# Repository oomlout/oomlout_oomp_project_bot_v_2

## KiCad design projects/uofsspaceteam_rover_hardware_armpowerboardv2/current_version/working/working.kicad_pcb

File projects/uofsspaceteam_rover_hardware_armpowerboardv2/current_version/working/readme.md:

# rover_hardware
 
## summary 
* id: uofsspaceteam_rover_hardware_armpowerboardv2
* user: uofsspaceteam
* name: rover_hardware
* board: armpowerboardv2
* repo: https://github.com/UofSSpaceTeam/rover-hardware
* src_file_repo_kicad_pcb: Projects/Arm/ArmPowerBoardV2/ArmPowerBoardV2.kicad_pcb
* src_file_repo_kicad_pcb_link: https://github.com/UofSSpaceTeam/rover-hardware/tree/master/Projects/Arm/ArmPowerBoardV2/ArmPowerBoardV2.kicad_pcb

* src_file_repo_sch: Projects/Arm/ArmPowerBoardV2/ArmPowerBoardV2.sch
* src_file_repo_sch_link: https://github.com/UofSSpaceTeam/rover-hardware/tree/master/Projects/Arm/ArmPowerBoardV2/ArmPowerBoardV2.sch
* full details link: https://github.com/oomlout/oomlout_oomp_project_bot_v_2/tree/main/projects/uofsspaceteam_rover_hardware_armpowerboardv2/current_version/working

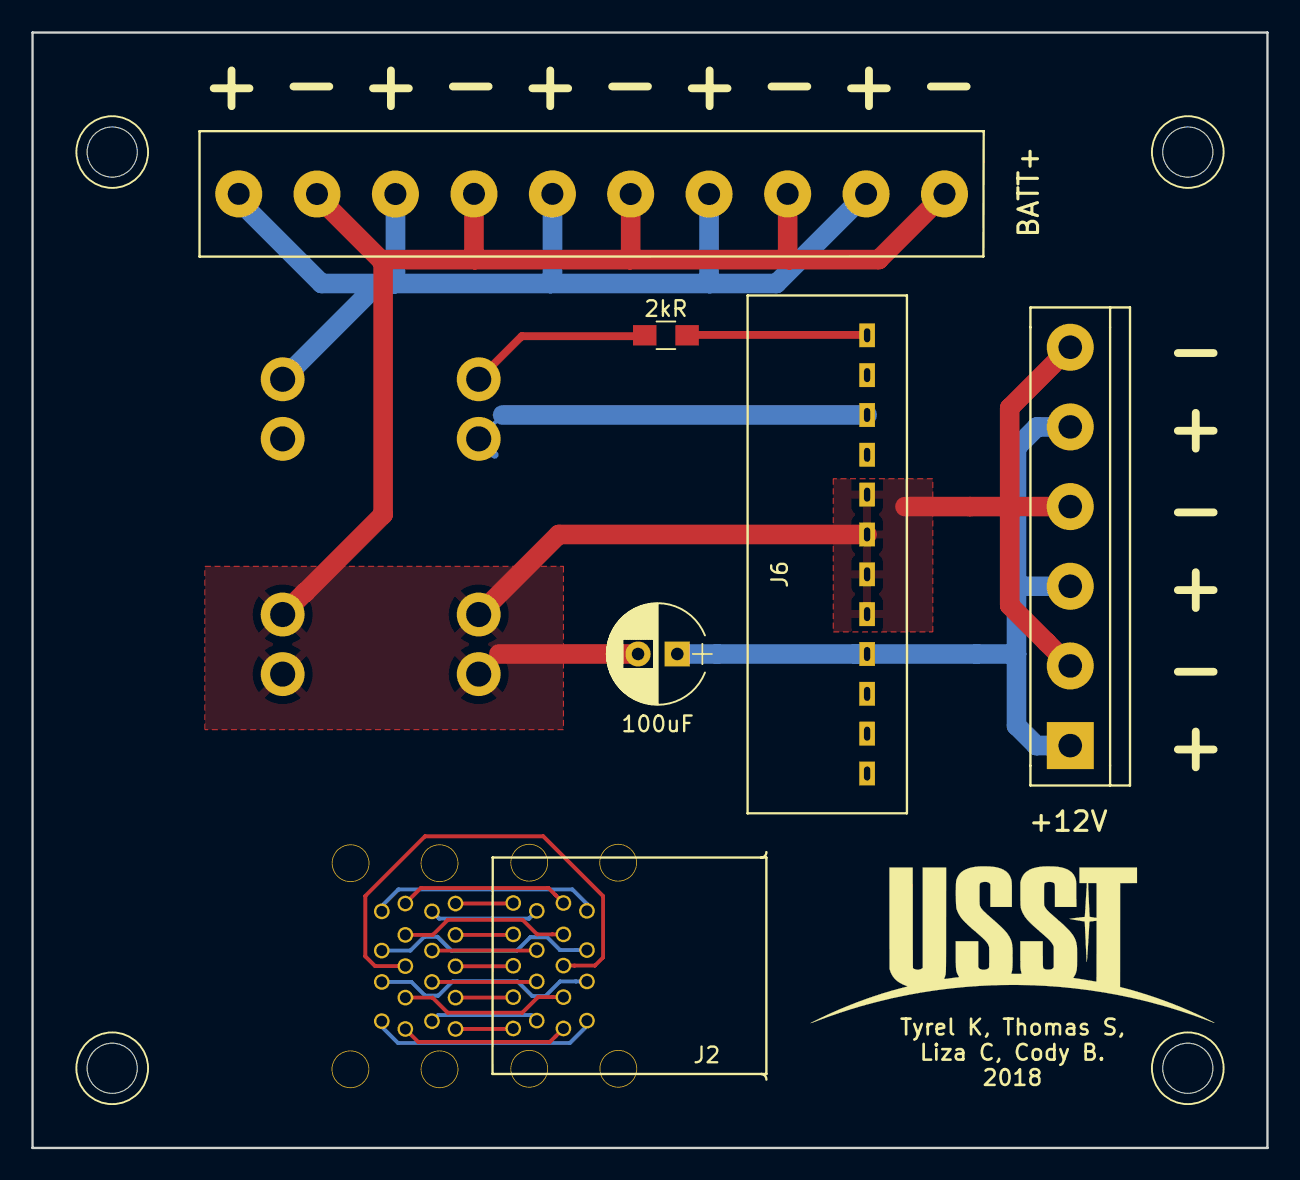
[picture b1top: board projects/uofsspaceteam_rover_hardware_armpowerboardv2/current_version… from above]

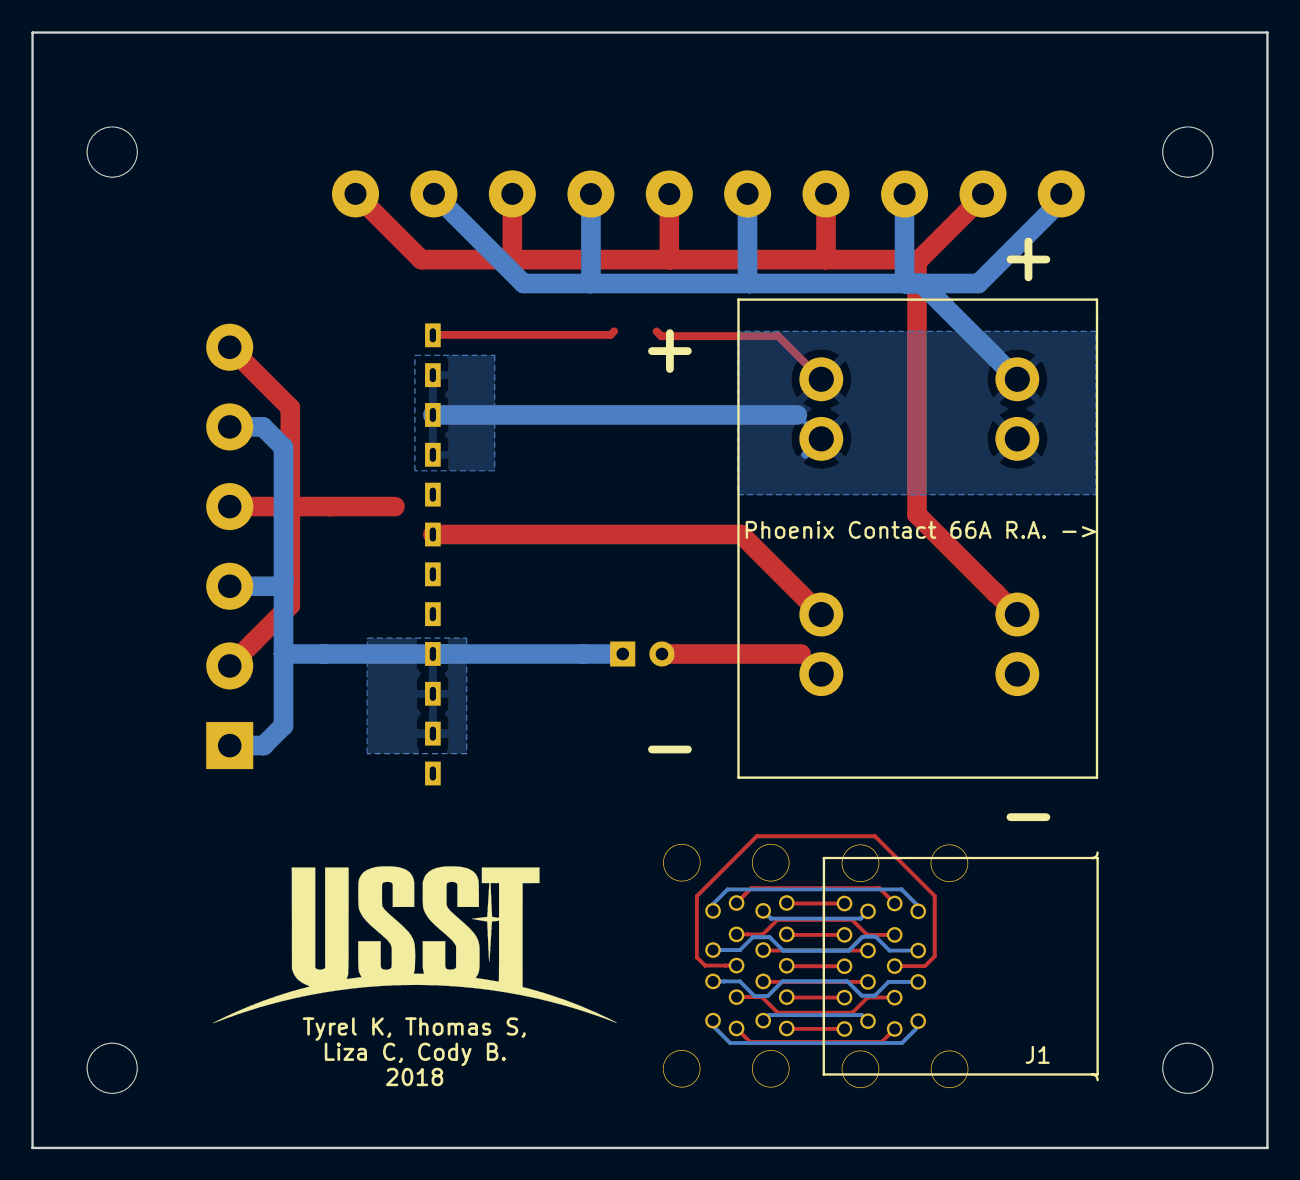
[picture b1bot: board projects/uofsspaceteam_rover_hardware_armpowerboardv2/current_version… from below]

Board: 2 copper layers, 78.7 x 71.1 mm, 8 parts (2 on the bottom side), 22 nets.

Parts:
2kR: 2kR; R_0805_HandSoldering
100uF: 100uF; CP_Radial_D6.3mm_P2.50mm
+12V: 1x6 Conn +12V; TerminalBlock_Pheonix_PT-5mm_6pol
BATT+: 1x10 Conn Batt+; Phoenix_Contact_Terminal_Block_1x10_1935242
J1, J2: USB 3.0 A Stacked; USB-A_3.0_Stacked_WM10420-ND
J6: R-6212P 12V DC Regulator; R-6212P_14-34VDC-12VDC_Converter
Phoenix Contact 66A R.A. ->: Phoenix Contact Batt; Phoenix_Contact_1770539

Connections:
+12V: 100uF.1, +12V.1, +12V.3, +12V.5, J6.9, J6.10, J6.11
BATT+: 2kR.1, BATT+.1, BATT+.3, BATT+.5, BATT+.7, BATT+.9, J6.2, J6.3, J6.4, Phoenix Contact 66A R.A. ->.1
GND: 100uF.2, +12V.2, +12V.4, +12V.6, BATT+.2, BATT+.4, BATT+.6, BATT+.8, BATT+.10, J6.5, J6.6, J6.7, J6.8, Phoenix Contact 66A R.A. ->.2
unnamed: J1.1, J2.1
unnamed: J1.2, J2.2
unnamed: J1.3, J2.3
unnamed: J1.4, J2.4
unnamed: J1.5, J2.5
unnamed: J1.6, J2.6
unnamed: J1.7, J2.7
unnamed: J1.8, J2.8
unnamed: J1.9, J2.9
unnamed: J1.10, J2.10
unnamed: J1.11, J2.11
unnamed: J1.12, J2.12
unnamed: J1.13, J2.13
unnamed: J1.14, J2.14
unnamed: J1.15, J2.15
unnamed: J1.16, J2.16
unnamed: J1.17, J2.17
unnamed: J1.18, J2.18
unnamed: 2kR.2, J6.1

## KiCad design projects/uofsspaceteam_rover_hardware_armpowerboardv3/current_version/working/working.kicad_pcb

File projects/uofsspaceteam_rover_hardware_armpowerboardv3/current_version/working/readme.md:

# rover_hardware
 
## summary 
* id: uofsspaceteam_rover_hardware_armpowerboardv3
* user: uofsspaceteam
* name: rover_hardware
* board: armpowerboardv3
* repo: https://github.com/UofSSpaceTeam/rover-hardware
* src_file_repo_kicad_pcb: Projects/Arm/ArmPowerBoardV3/ArmPowerBoardV3/ArmPowerBoardV3.kicad_pcb
* src_file_repo_kicad_pcb_link: https://github.com/UofSSpaceTeam/rover-hardware/tree/master/Projects/Arm/ArmPowerBoardV3/ArmPowerBoardV3/ArmPowerBoardV3.kicad_pcb

* src_file_repo_brd: Projects/Arm/ArmPowerBoardV3/ArmPowerBoardV3/FT232RL_USB_Breakout-V_3.7/Hardware/FT232R-Breakout.brd
* src_file_repo_brd_link: https://github.com/UofSSpaceTeam/rover-hardware/tree/master/Projects/Arm/ArmPowerBoardV3/ArmPowerBoardV3/FT232RL_USB_Breakout-V_3.7/Hardware/FT232R-Breakout.brd
* src_file_repo_sch: Projects/Arm/ArmPowerBoardV3/ArmPowerBoardV3/ArmPowerBoardV3.sch
* src_file_repo_sch_link: https://github.com/UofSSpaceTeam/rover-hardware/tree/master/Projects/Arm/ArmPowerBoardV3/ArmPowerBoardV3/ArmPowerBoardV3.sch
* full details link: https://github.com/oomlout/oomlout_oomp_project_bot_v_2/tree/main/projects/uofsspaceteam_rover_hardware_armpowerboardv3/current_version/working

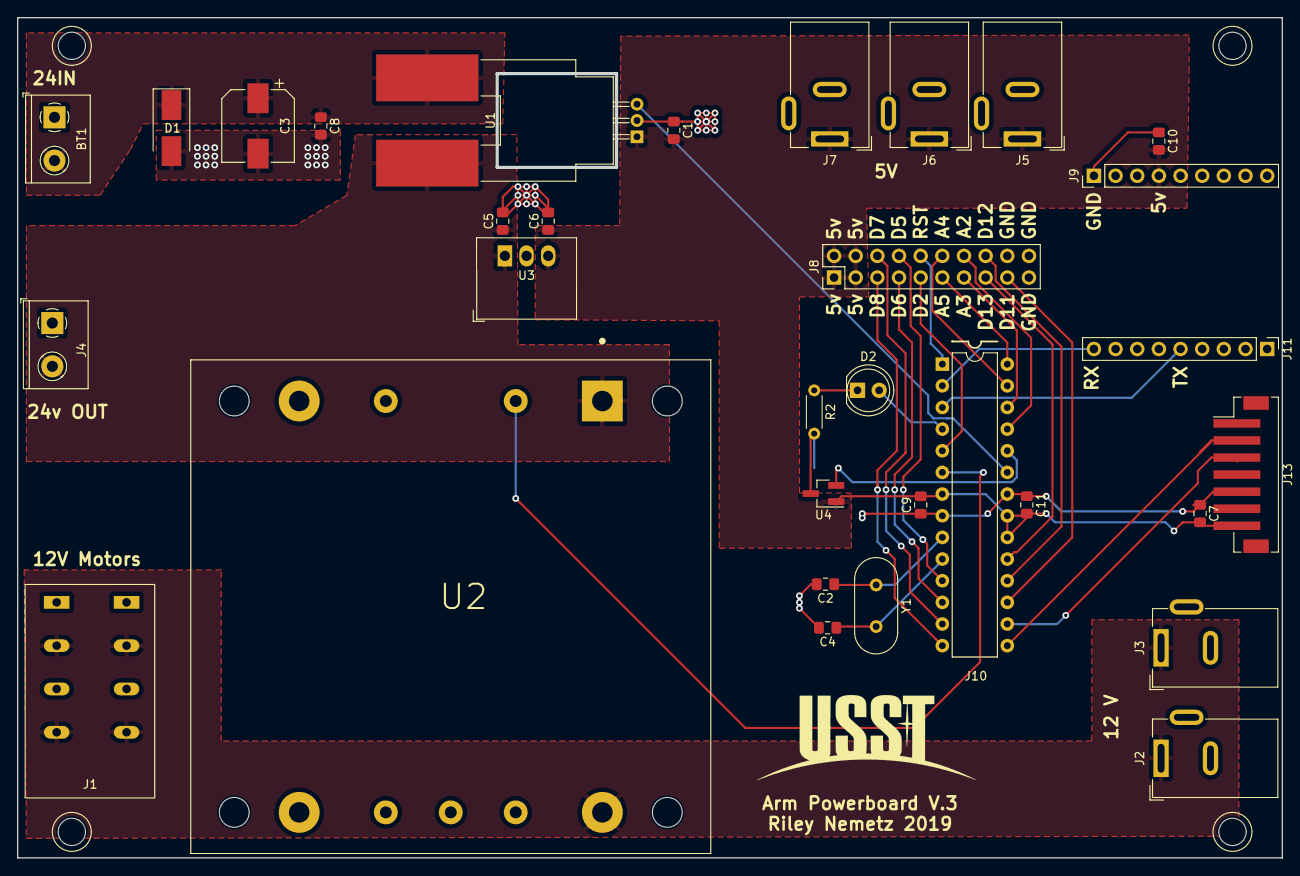
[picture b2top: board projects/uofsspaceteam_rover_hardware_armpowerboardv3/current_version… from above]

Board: 2 copper layers, 148.3 x 98.6 mm, 32 parts (0 on the bottom side), 30 nets.

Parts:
BT1: 24vin; TerminalBlock_1x02_P5.08mm_Horizontal
C1, C7, C9, C10, C11: 100nF; C_0805_2012Metric_Pad1.15x1.40mm_HandSolder
C2, C4: 22pF; C_0805_2012Metric_Pad1.15x1.40mm_HandSolder
C3: 220uF; CP_Elec_8x10
C5, C6: 10pF; C_0805_2012Metric_Pad1.15x1.40mm_HandSolder
C8: 10 uF; C_0805_2012Metric_Pad1.15x1.40mm_HandSolder
D1: D_Zener; D_SMB_Handsoldering
D2: LED; LED_D5.0mm_IRGrey
J1: Screw_Terminal_01x04; TerminalBlock_Big4pin
J2, J3, J5, J6, J7: Barrel_Jack; BarrelJack_Wuerth_6941xx301002
J4: Screw_Terminal_01x02; TerminalBlock_1x02_P5.08mm_Horizontal
J8: Gpio out; PinHeader_2x10_P2.54mm_Vertical
J9: Breakout L; PinHeader_1x09_P2.54mm_Vertical
J10: Atmega Holder; DIP-28_W7.62mm
J11: Breakout R; PinHeader_1x09_P2.54mm_Vertical
J13: JST serial; JST_PH_B7B-PH-SM4-TB_1x07-1MP_P2.00mm_Vertical
R2: R; R_Axial_DIN0204_L3.6mm_D1.6mm_P5.08mm_Horizontal
U1: ACS758; Allegro_CB_PSF
U2: VHB200W-Q24-S12; CONV_VHB200W-Q24-S12
U3: V7805-1000
U4: Temp sense; SOT-23_Handsoldering
Y1: Crystal; Crystal_HC49-U_Vertical

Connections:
5v+: C1.2, C6.1, C7.2, C9.2, C10.2, C11.2, J5.1, J6.1, J7.1, J8.1, J8.2, J8.3, J8.4, J9.4, J10.7, J10.20, J10.21, J13.7, U1.1, U3.3, U4.1
12v+: J1.2, J1.4, J2.1, J3.1, U2.9
12v-: J1.1, J1.3, J2.2, J3.2, U2.5
24v: C5.1, J4.2, U1.5, U2.1, U3.1
GND: BT1.1, C1.1, C2.2, C3.2, C4.2, C5.2, C6.2, C7.1, C8.2, C9.1, C10.1, C11.1, D1.2, J4.1, J5.2, J6.2, J7.2, J8.18, J8.19, J8.20, J9.1, J10.8, J10.22, J13.5, R2.2, U1.2, U2.4, U3.2, U4.3
ISense: J10.23, U1.3
unnamed: BT1.2, C3.1, C8.1, D1.1, U1.4
unnamed: C2.1, J10.9, Y1.1
unnamed: C4.1, J10.10, Y1.2
unnamed: D2.1, R2.1
unnamed: D2.2, J10.4
unnamed: J8.10, J10.1
unnamed: J8.9, J10.5
unnamed: J8.8, J10.11
unnamed: J8.7, J10.12
unnamed: J8.6, J10.13
unnamed: J8.5, J10.14
unnamed: J8.17, J10.17
unnamed: J8.16, J10.18
unnamed: J8.15, J10.19
unnamed: J8.14, J10.25
unnamed: J8.13, J10.26
unnamed: J8.12, J10.27
unnamed: J8.11, J10.28
ONoff: J10.6, U2.2
RX1: J10.15, J13.2
Rx: J10.2, J11.9
TX1: J10.16, J13.3
TempSense: J10.24, U4.2
Tx: J10.3, J11.5

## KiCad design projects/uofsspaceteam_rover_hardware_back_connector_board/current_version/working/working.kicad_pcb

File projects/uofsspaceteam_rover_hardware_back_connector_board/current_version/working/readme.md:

# rover_hardware
 
## summary 
* id: uofsspaceteam_rover_hardware_back_connector_board
* user: uofsspaceteam
* name: rover_hardware
* board: back_connector_board
* repo: https://github.com/UofSSpaceTeam/rover-hardware
* src_file_repo_kicad_pcb: Projects/Power Distribution/Back Connector Board/Back Connector Board.kicad_pcb
* src_file_repo_kicad_pcb_link: https://github.com/UofSSpaceTeam/rover-hardware/tree/master/Projects/Power Distribution/Back Connector Board/Back Connector Board.kicad_pcb
* src_file_repo_kicad_sch: Projects/Power Distribution/ACS712_Testing/ACS712.kicad_sch
* src_file_repo_kicad_sch_link: https://github.com/UofSSpaceTeam/rover-hardware/tree/master/Projects/Power Distribution/ACS712_Testing/ACS712.kicad_sch
* src_file_repo_brd: Projects/Communication/KiCad_USB/modified_eagle_files/RH025.1.brd
* src_file_repo_brd_link: https://github.com/UofSSpaceTeam/rover-hardware/tree/master/Projects/Communication/KiCad_USB/modified_eagle_files/RH025.1.brd
* src_file_repo_sch: Projects/Power Distribution/Back Connector Board/Back Connector Board.sch
* src_file_repo_sch_link: https://github.com/UofSSpaceTeam/rover-hardware/tree/master/Projects/Power Distribution/Back Connector Board/Back Connector Board.sch
* full details link: https://github.com/oomlout/oomlout_oomp_project_bot_v_2/tree/main/projects/uofsspaceteam_rover_hardware_back_connector_board/current_version/working

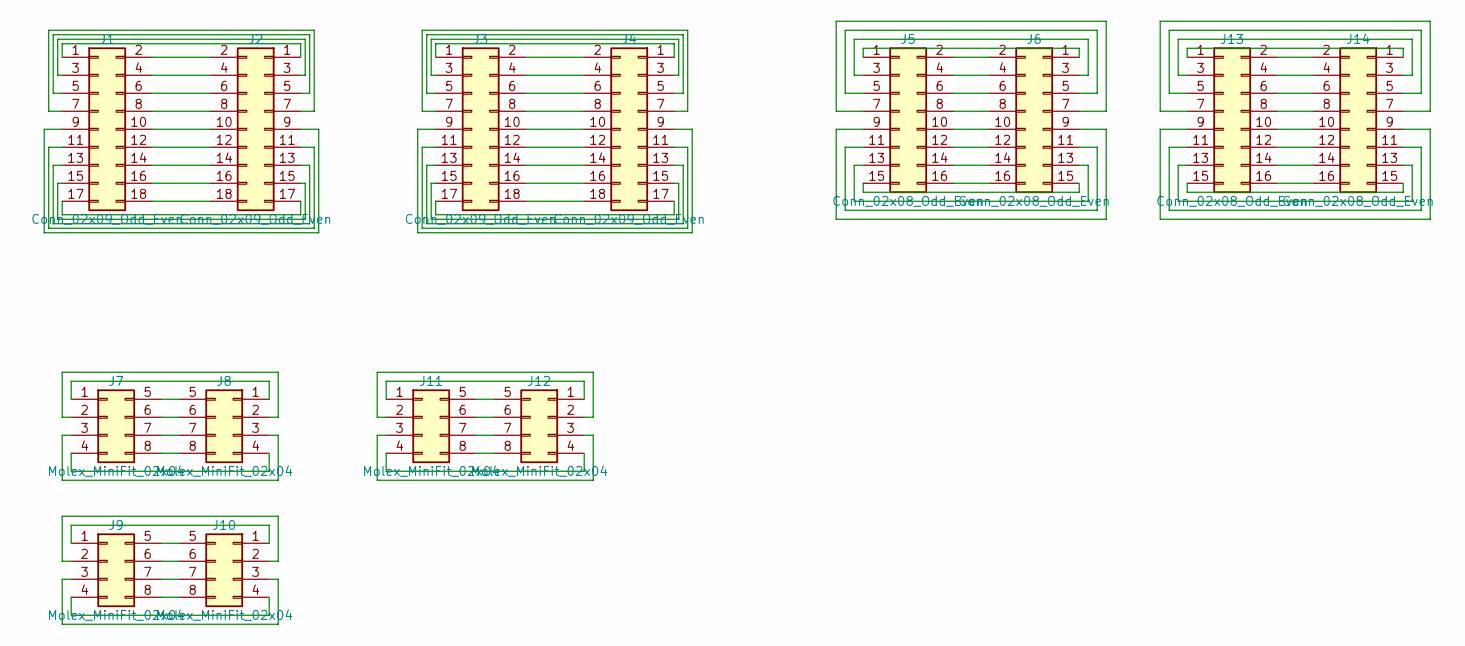
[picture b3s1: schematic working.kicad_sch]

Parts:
J1, J2, J3, J4: Conn_02x09_Odd_Even; USBA_3.0_Stacked_Vertical-Molex_48409
J5, J6, J13, J14: Conn_02x08_Odd_Even; Pin_Header_Straight_2x08_Pitch2.54mm
J7, J8, J9, J10, J11, J12: Molex_MiniFit_02x04; Molex_MiniFit-JR_5566-08A_02x04x4.2_Vertical

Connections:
unnamed: J1.1, J2.1
unnamed: J1.2, J2.2
unnamed: J1.3, J2.3
unnamed: J1.4, J2.4
unnamed: J1.5, J2.5
unnamed: J1.6, J2.6
unnamed: J1.7, J2.7
unnamed: J1.8, J2.8
unnamed: J1.9, J2.9
unnamed: J1.10, J2.10
unnamed: J1.11, J2.11
unnamed: J1.12, J2.12
unnamed: J1.13, J2.13
unnamed: J1.14, J2.14
unnamed: J1.15, J2.15
unnamed: J1.16, J2.16
unnamed: J1.17, J2.17
unnamed: J1.18, J2.18
unnamed: J3.1, J4.1
unnamed: J3.2, J4.2
unnamed: J3.3, J4.3
unnamed: J3.4, J4.4
unnamed: J3.5, J4.5
unnamed: J3.6, J4.6
unnamed: J3.7, J4.7
unnamed: J3.8, J4.8
unnamed: J3.9, J4.9
unnamed: J3.10, J4.10
unnamed: J3.11, J4.11
unnamed: J3.12, J4.12
unnamed: J3.13, J4.13
unnamed: J3.14, J4.14
unnamed: J3.15, J4.15
unnamed: J3.16, J4.16
unnamed: J3.17, J4.17
unnamed: J3.18, J4.18
unnamed: J5.1, J6.1
unnamed: J5.2, J6.2
unnamed: J5.3, J6.3
unnamed: J5.4, J6.4
unnamed: J5.5, J6.5
unnamed: J5.6, J6.6
unnamed: J5.7, J6.7
unnamed: J5.8, J6.8
unnamed: J5.9, J6.9
unnamed: J5.10, J6.10
unnamed: J5.11, J6.11
unnamed: J5.12, J6.12
unnamed: J5.13, J6.13
unnamed: J5.14, J6.14
unnamed: J5.15, J6.15
unnamed: J5.16, J6.16
unnamed: J7.1, J8.1
unnamed: J7.2, J8.2
unnamed: J7.3, J8.3
unnamed: J7.4, J8.4
unnamed: J7.5, J8.5
unnamed: J7.6, J8.6
unnamed: J7.7, J8.7
unnamed: J7.8, J8.8
unnamed: J9.1, J10.1
unnamed: J9.2, J10.2
unnamed: J9.3, J10.3
unnamed: J9.4, J10.4
unnamed: J9.5, J10.5
unnamed: J9.6, J10.6
unnamed: J9.7, J10.7
unnamed: J9.8, J10.8
unnamed: J11.1, J12.1
unnamed: J11.2, J12.2
unnamed: J11.3, J12.3
unnamed: J11.4, J12.4
unnamed: J11.5, J12.5
unnamed: J11.6, J12.6
unnamed: J11.7, J12.7
unnamed: J11.8, J12.8
unnamed: J13.1, J14.1
unnamed: J13.2, J14.2
unnamed: J13.3, J14.3
unnamed: J13.4, J14.4
unnamed: J13.5, J14.5
unnamed: J13.6, J14.6
unnamed: J13.7, J14.7
unnamed: J13.8, J14.8
unnamed: J13.9, J14.9
unnamed: J13.10, J14.10
unnamed: J13.11, J14.11
unnamed: J13.12, J14.12
unnamed: J13.13, J14.13
unnamed: J13.14, J14.14
unnamed: J13.15, J14.15
unnamed: J13.16, J14.16

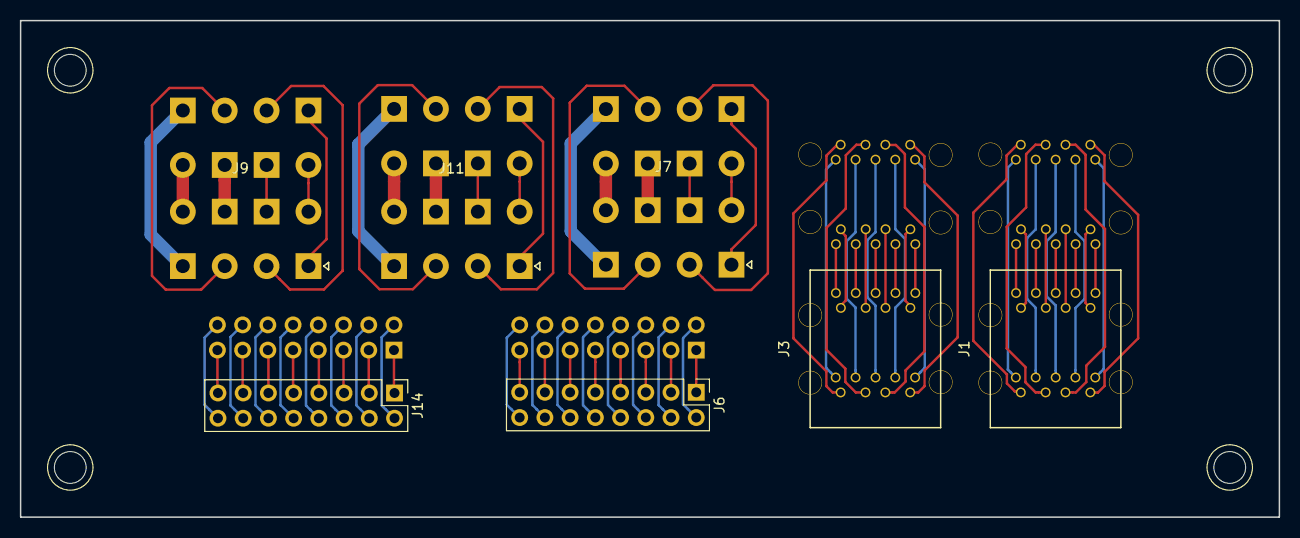
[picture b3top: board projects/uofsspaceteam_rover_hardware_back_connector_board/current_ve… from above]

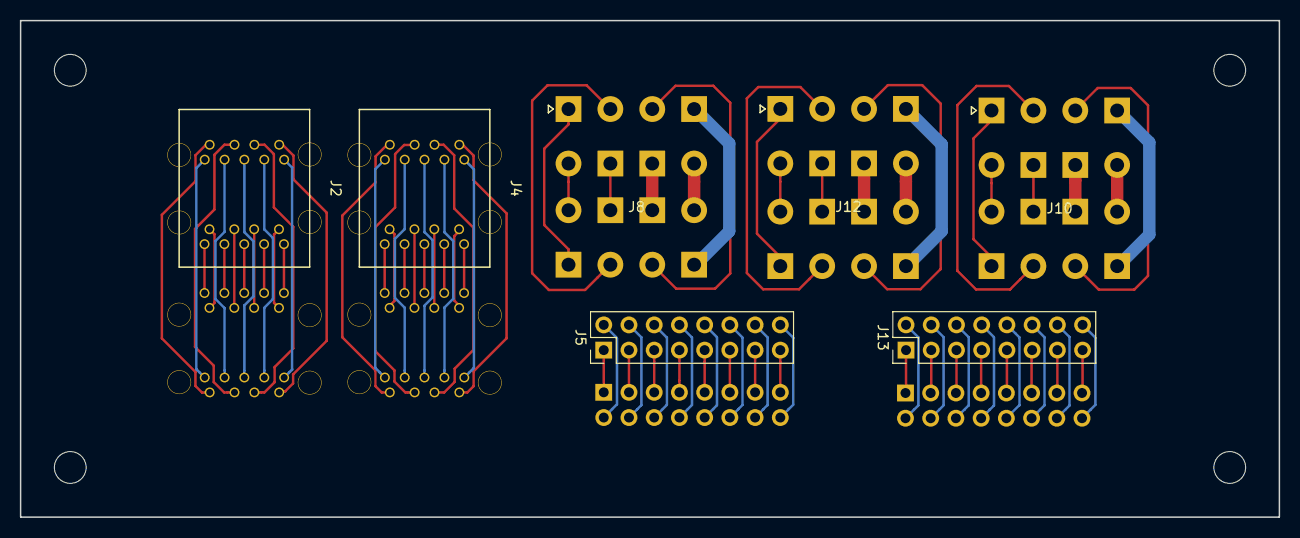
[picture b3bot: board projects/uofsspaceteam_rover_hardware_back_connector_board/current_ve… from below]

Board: 2 copper layers, 126.8 x 50.0 mm, 14 parts (7 on the bottom side), 92 nets.
